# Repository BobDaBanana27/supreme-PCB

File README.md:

# supreme-PCB
For Hack Club Half-Life
# PCBs – devlog

| Week | Tier | Hours logged | Entries |
| --- | --- | --- | --- |
| Week 1 | Tier 1 | 7h | 1 |

## Contents

The first hour consisted of nothing much but research into parts and fitting within the budget. I ended up settling on these parts, as seen in the image below. Hours 2-5 all consisted of working inside KiCad to build and test the PCB. For the PCB layout file, I built out a standard 1.6 mm thick board on an A4 sheet using KiCad. On the board, I used a USB-C connector for power and data, the RP2040-Zero as the computer, a couple of rotary encoders for dial controls, six tactile switches for the macro buttons, and an OLED display for visuals. To wrap up the power side, I added a 3.3V regulator along with its supporting components.

 I set standard DRC rules in the project config file. Tracking a minimum of 0.2 mm, zero clearance, and 0.5 mm spacing from the board edge, while the default net class runs 0.2 mm tracks, 0.2 mm clearance, and uses 0.3 mm drill / 0.6 mm outer diameter vias to tie everything smoothly over to the main schematic file.

For the schematic, I split the layout into neat, manageable blocks covering USB power and regulation, the RP2040 controller, custom buttons, rotary dials, and a status display. Finally, I wired up all the key nets, including VBUS, +3V3, GND, the button lines, the encoder pins, ENC1_PUSH, and the I2C bus lines.

BOM.md: 

# PCBs – bill of materials

<!-- Generated by Half Life from project cmuvnrmow010x01o92wi5b3kl. Edits here are overwritten on the next sync. -->
<!-- Generated: 2026-10-12T02:24:15.047Z -->

> [!NOTE]
> This parts list is mirrored from [Half Life](https://halflife.hackclub.com). Editing it here will not change the platform's copy, and the next sync overwrites this file.

| Week | Tier | Parts funding |
| --- | --- | --- |
| Week 1 | Tier 1 | $30.00 |

| Part | What it's for | Qty | Unit | Total | Vendor |
| --- | --- | --- | --- | --- | --- |
| [USB4120-03-C USB Connector](https://www.digikey.ca/en/products/detail/gct/USB4120-03-C/13547390) | USB Connector | 1 | $1.33 | $1.33 | [Digikey](https://www.digikey.ca/en/products/detail/gct/USB4120-03-C/13547390) |
| [RP2040-ZERO MicroController Board](https://www.amazon.ca/RP2040-Zero-Compatible-Raspberry-Pico/dp/B0B2CVPDH6?source=ps-sl-shoppingads-lpcontext&ref_=fplfs&psc=1&smid=A29AOP4GIE7DX6) | The Brain/Computer | 1 | $3.00 | $3.00 | [Amazon](https://www.amazon.ca/RP2040-Zero-Compatible-Raspberry-Pico/dp/B0B2CVPDH6?source=ps-sl-shoppingads-lpcontext&ref_=fplfs&psc=1&smid=A29AOP4GIE7DX6) |
| [PEC11R-4215F-S0024](https://www.digikey.ca/en/products/detail/bourns-inc/PEC12R-4215F-S0024/6153388?gclsrc=aw.ds&gad_source=4&gad_campaignid=20572521725&gbraid=0AAAAADrbLlgIql0iS6lTDUUxeblYrz86A&gclid=CjwKCAjw56zWBhB0EiwAdPOQOajHSczooKdhYfznTe8mktGKJKbMOTt4XMKWzR7uopAIZzpSzCUd4RoCLYwQAvD_BwE) | Rotary Encoders (Dial Controls) | 2 | $1.50 | $3.00 | [Digikey](https://www.digikey.ca/en/products/detail/bourns-inc/PEC12R-4215F-S0024/6153388?gclsrc=aw.ds&gad_source=4&gad_campaignid=20572521725&gbraid=0AAAAADrbLlgIql0iS6lTDUUxeblYrz86A&gclid=CjwKCAjw56zWBhB0EiwAdPOQOajHSczooKdhYfznTe8mktGKJKbMOTt4XMKWzR7uopAIZzpSzCUd4RoCLYwQAvD_BwE) |
| [KMR221GLFS](https://www.digikey.ca/en/products/detail/c-k/KMR221G-LFS/550472) | Tactile buttons | 6 | $0.80 | $4.80 | [Digikey](https://www.digikey.ca/en/products/detail/c-k/KMR221G-LFS/550472) |
| [HS96L03W2C03 OLED Display](https://jlcpcb.com/partdetail/HS-0_96_OLED_IIC/C5248080) | OLED Display | 1 | $2.00 | $2.00 | [JLCPCB](https://jlcpcb.com/partdetail/HS-0_96_OLED_IIC/C5248080) |
| [TC1262-3.3VDB Voltage Regulator](https://www.digikey.ca/en/products/detail/microchip-technology/TC1262-3-3VDB/1980071) | Regulates the voltage. | 1 | $1.00 | $1.00 | [Digikey](https://www.digikey.ca/en/products/detail/microchip-technology/TC1262-3-3VDB/1980071) |
| [CFM14JT5K10](https://www.digikey.ca/en/products/detail/stackpole-electronics-inc/CFM14JT5K10/1742231) | 5.1k Resistors | 2 | $0.16 | $0.32 | [Digikey](https://www.digikey.ca/en/products/detail/stackpole-electronics-inc/CFM14JT5K10/1742231) |
| [100nF Capacitor](https://www.amazon.ca/100pcs-50V-Ceramic-Capacitor-100nF/dp/B0C5TD12T1?th=1) | Capacitor. | 1 | $2.50 | $2.50 | [Amazon](https://www.amazon.ca/100pcs-50V-Ceramic-Capacitor-100nF/dp/B0C5TD12T1?th=1) |
| **Parts subtotal** | — | — | — | **$17.95** | — |
| **Tax & shipping** | — | — | — | **$12.04** | — |
| **Total** | — | — | — | **$29.99** | — |

$0.01 left of the tier's funding.

EDIT: The image at the top **is** the final PCB.

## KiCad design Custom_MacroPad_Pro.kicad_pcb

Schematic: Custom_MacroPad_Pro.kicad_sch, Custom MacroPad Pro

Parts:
C1: 100nF; C0805
R1, R2: 5.1k; R0805
SW1, SW2, SW3, SW4, SW5, SW6: KMR221GLFS; KEY-SMD_KMR2XXGXXX; MPN KMR221GLFS; LCSC C72443
SW7, SW8: PEC11R-4215F-S0024; SW-TH_5P-L12.5-W13.4-P2.50-LS14.5; MPN PEC11R-4215F-S0024; LCSC C143790
U1: RP2040-ZERO; COMM-SMD_RP2040-ZERO; MPN RP2040-Zero; LCSC C5350143
U2: HS96L03W2C03; OLED-TH_L27.8-W27.2-P2.54_C9900033791; MPN HS96L03W2C03; LCSC C5248080
U3: TC1262-3.3VDB; SOT-223-3_L6.5-W3.5-P3.05-LS7.0; MPN TC1262-3.3VDB; LCSC C638655
USB1: USB4120-03-C; TYPE-C-SMD_USB4120-03-C; MPN USB4120-03-C; LCSC C3445864

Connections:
+3.3V: C1.1, U1.21 (3V3), U2.2 (VCC), U3.3 (VOUT)
BTN1: SW1.1, SW1.3, U1.1 (GP0)
BTN2: SW2.1, SW2.3, U1.2 (GP1)
BTN3: SW3.1, SW3.3, U1.3 (GP2)
BTN4: SW4.1, SW4.3, U1.4 (GP3)
BTN5: SW5.1, SW5.3, U1.5 (GP4)
BTN6: SW6.1, SW6.3, U1.6 (GP5)
ENC1_A: SW7.1 (A), SW7.3 (B), U1.7 (GP6)
ENC1_B: SW7.2 (C), U1.8 (GP7)
ENC1_PUSH: SW7.4 (1), U1.9 (GP8)
ENC2_A: SW8.1 (A), SW8.3 (B), U1.10 (GP9)
ENC2_B: SW8.2 (C), U1.11 (GP10)
ENC2_PUSH: SW8.4 (1), U1.12 (GP11)
GND: C1.2, R1.1, R2.2, SW1.2, SW1.4, SW1.5, SW2.2, SW2.4, SW2.5, SW3.2, SW3.4, SW3.5, SW4.2, SW4.4, SW4.5, SW5.2, SW5.4, SW5.5, SW6.2, SW6.4, SW6.5, SW7.5 (2), SW7.7, SW7.8, SW8.5 (2), SW8.7, SW8.8, U1.22 (GND), U2.1 (GND), USB1.A1 (GND), USB1.A12 (GND), USB1.B1 (GND), USB1.B12 (GND)
I2C_SCL: U1.13 (GP12), U2.3 (SCL)
I2C_SDA: U1.14 (GP13), U2.4 (SDA)
N_0A49092D: USB1.B7 (Dn2)
N_3A9D9795: U1.15 (GP14)
N_3D9D9C4E: U1.18 (GP27)
N_3E9D9DE1: U1.19 (GP28)
N_5B14399E: USB1.0
N_7A507542: USB1.A7 (Dn1)
N_7B5076D5: USB1.A6 (Dp1)
N_7D5079FB: USB1.A8 (SBU1)
N_96F0205B: R1.2, USB1.A5 (CC1)
N_379D92DC: U1.16 (GP15)
N_389D946F: U1.17 (GP26)
N_638ACE93: U3.4 (GND)
N_698AD805: U3.2 (GND)
N_0949079A: USB1.B6 (Dp2)
N_BF310684: R2.1, USB1.B5 (CC2)
N_CF9AB08D: U1.20 (GP29)
N_FB48F190: USB1.B8 (SBU2)
VBUS: U1.23 (5V), U3.1 (VIN), USB1.A4 (VBUS), USB1.A9 (VBUS), USB1.B4 (VBUS), USB1.B9 (VBUS)

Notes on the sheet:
PROTOFLOW_REGION:eyJpZCI6ImZpbmFsLXNlY3Rpb24tMWMyYzAzOThiZGE0NDU2ZSIsIm5hbWUiOiJVU0IgUG93ZXIgYW5kIFJlZ3VsYXRpb24iLCJ4MSI6NjA5LjU5OTk5OTk5OTk5OTksInkxIjo1OTYuOSwieDIiOjE0NDcuNzk5OTk5OTk5OTk5NywieTIiOjE0NjAuNSwiY29sb3IiOjQyODMyNjkzMjUsImRlc2NyaXB0aW9uIjpudWxsLCJjb21wb25lbnRJZHMiOlsiYjYwMjE5NzQtYTJkNy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
USB Power and Regulation
PROTOFLOW_REGION:eyJpZCI6ImZpbmFsLXNlY3Rpb24tNGY4NzU4ODRmY2ZmOTIxZSIsIm5hbWUiOiJSUDIwNDAgQ29udHJvbGxlciIsIngxIjoxNTQ5LjM5OTk5OTk5OTk5OTksInkxIjo1OTYuOSwieDIiOjIxOTcuMSwieTIiOjE0NjAuNSwiY29sb3IiOjQyODI0Mjc1MDQsImRlc2NyaXB0aW9uIjpudWxsLCJjb21wb25lbnRJZHMiOlsiMGM4ZWRiZmEtZTUxYS00NTEwLWI5M2UtMTM5ZGMzMG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
RP2040 Controller
PROTOFLOW_REGION:eyJpZCI6ImZpbmFsLXNlY3Rpb24tNGVhMzRlOTkwNzljMTIzNSIsIm5hbWUiOiJDdXN0b20gQnV0dG9ucyIsIngxIjoyMjk4LjcsInkxIjo1OTYuOSwieDIiOjM1OTQuMSwieTIiOjE0NjAuNSwiY29sb3IiOjQyODkzNjAwNzcsImRlc2NyaXB0aW9uIjpudWxsLCJjb21wb25lbnRJZHMiOlsiNzkzZmQ4YTAtODJmNS00YzE0LWE1ZjItNjczZWU3MThjM2U2IiwiZWUxNzhhZm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
Custom Buttons
PROTOFLOW_REGION:eyJpZCI6ImZpbmFsLXNlY3Rpb24tOTFiMTJiYzkyYzc4ZmY3YiIsIm5hbWUiOiJSb3RhcnkgRGlhbHMiLCJ4MSI6NjA5LjU5OTk5OTk5OTk5OTksInkxIjoxNTYyLjEsIngyIjoxNDQ3Ljc5OTk5OTk5OTk5OTcsInkyIjoyMTcxLjcsImNvbG9yIjo0MjkxNDAyNTUyLCJkZXNjcmlwdGlvbiI6bnVsbCwiY29tcG9uZW50SWRzIjpbIjVmNzgxMjgyLTQ0ZjMtNGYxYy04YzM2LT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
Rotary Dials
PROTOFLOW_REGION:eyJpZCI6ImZpbmFsLXNlY3Rpb24tMWQ5ZTQ1ZjBiZjk0ODllMiIsIm5hbWUiOiJTdGF0dXMgRGlzcGxheSIsIngxIjoxNTQ5LjM5OTk5OTk5OTk5OTksInkxIjoxNTYyLjEsIngyIjoyMTk3LjEsInkyIjoyMTcxLjcsImNvbG9yIjo0MjkyMTA2ODcwLCJkZXNjcmlwdGlvbiI6bnVsbCwiY29tcG9uZW50SWRzIjpbImU0NmM1MzBlLTJhYTUtNDQzYy05ZmE4LThlNTE5ZmYxMj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
Status Display

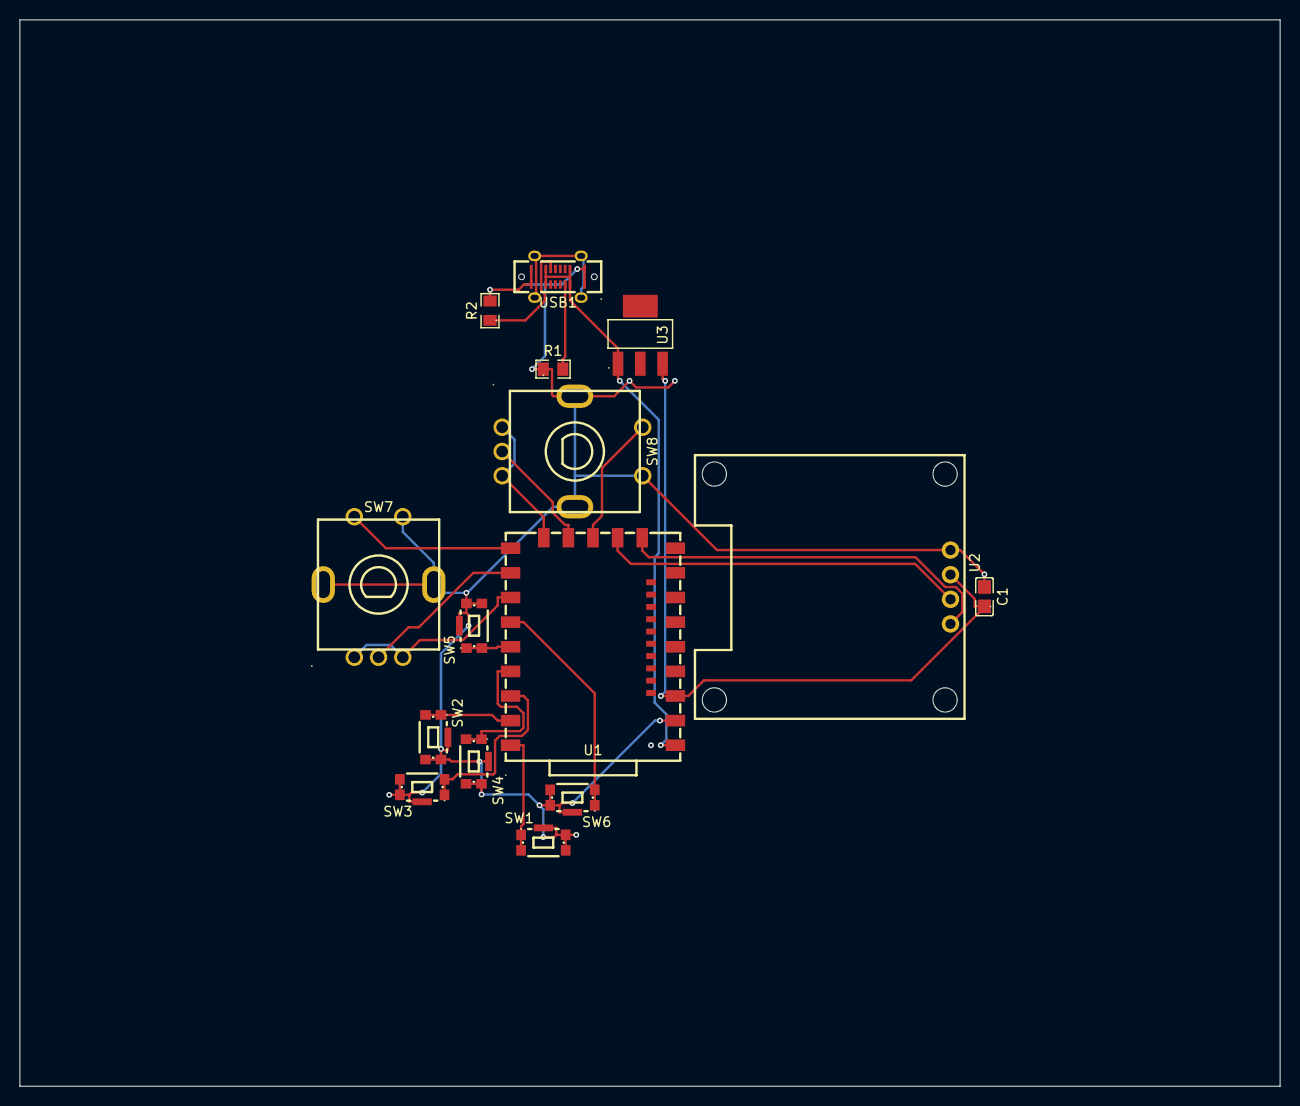
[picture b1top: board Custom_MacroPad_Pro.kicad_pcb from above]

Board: 2 copper layers, 130.0 x 110.0 mm, 15 parts (0 on the bottom side), 19 nets.

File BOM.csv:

,Part,Serial Number / Type,Quantity,Approx. Cost USD (Total)
,USB Connector,USB4120-03-C,1,$1
,Microcontroller Board,RP2040-ZERO,1,$5
,Rotary Encoders,PEC11R-4215F-S0024,2,$6
,Tactile Buttons,KMR221GLFS,6,$6
,OLED Display,HS96L03W2C03,1,$3
,Voltage Regulator,TC1262-3.3VDB,1,$1
,Resistors,5.1k Resistors,2,$2
,Capacitor,100nF Capacitor,1,$2
Total,,,,$26
